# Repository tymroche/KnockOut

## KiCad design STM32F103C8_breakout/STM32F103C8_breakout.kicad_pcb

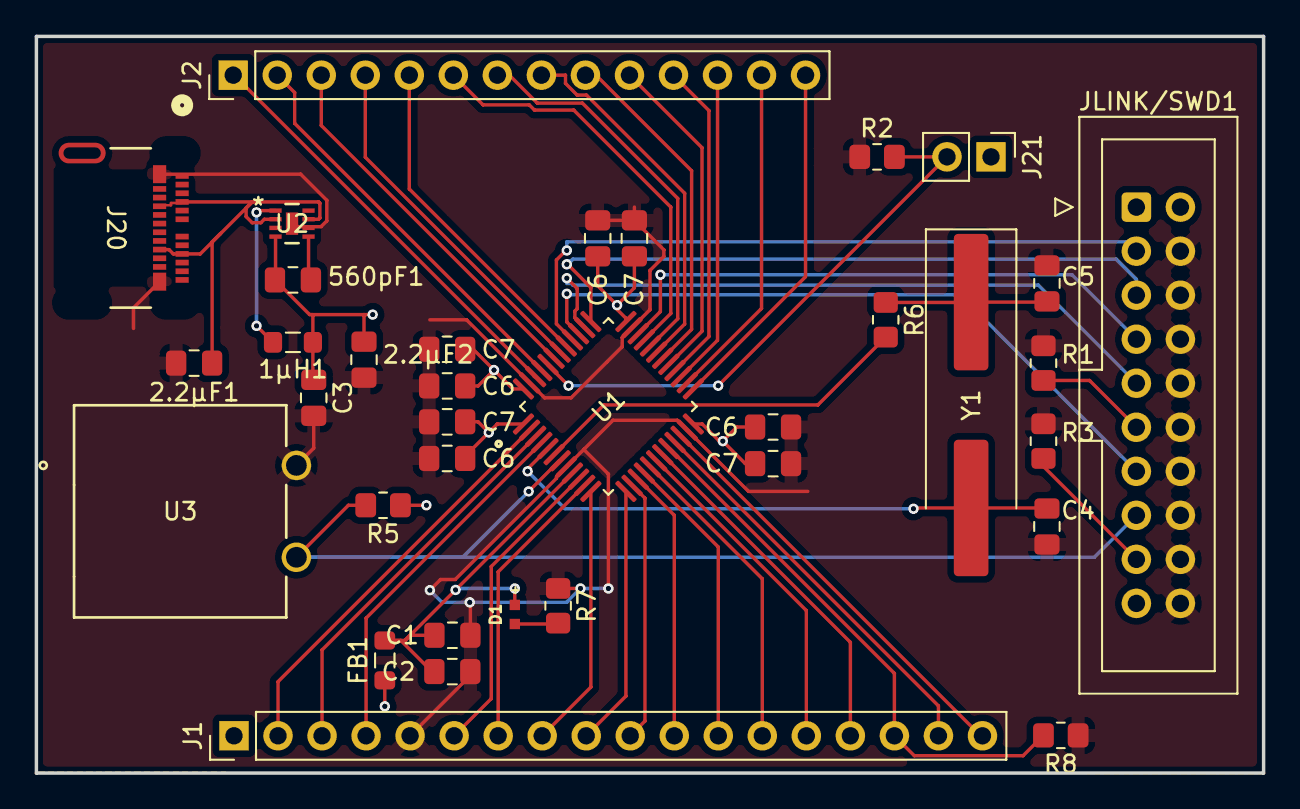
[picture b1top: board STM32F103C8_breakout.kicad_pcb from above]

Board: 2 copper layers, 70.8 x 42.5 mm, 35 parts (0 on the bottom side), 49 nets.

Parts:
1µH1: L_Small; L_0805_2012Metric_Pad1.05x1.20mm_HandSolder
2.2µF1, 2.2µF2, 560pF1: C_Small_US; C_0805_2012Metric_Pad1.18x1.45mm_HandSolder
C1: 1μF; C_0805_2012Metric_Pad1.18x1.45mm_HandSolder
C2, C3, C6, C6#2, C6#3, C6#4: 100nF; C_0805_2012Metric_Pad1.18x1.45mm_HandSolder
C4, C5: 20pF; C_0805_2012Metric_Pad1.18x1.45mm_HandSolder
C7, C7#2, C7#3, C7#4: 10μF; C_0805_2012Metric_Pad1.18x1.45mm_HandSolder
D1: WL-SMCC_0402
FB1: FerriteBead_Small; L_0805_2012Metric_Pad1.05x1.20mm_HandSolder
J1: Conn_01x18_Pin; PinHeader_1x18_P2.54mm_Vertical
J2: Conn_01x14_Pin; PinHeader_1x14_P2.54mm_Vertical
J20: USB-C; CONN_1054500101_MOL
J21: Conn_01x02_Pin; PinHeader_1x02_P2.54mm_Vertical
JLINK/SWD1: IDC-Header_2x10_P2.54mm_Vertical
R1, R2, R3, R5, R7, R8: 10kΩ; R_0805_2012Metric_Pad1.20x1.40mm_HandSolder
R6: 400Ω; R_0805_2012Metric_Pad1.20x1.40mm_HandSolder
U1: STM32F103C8T6; QFP50P900X900X160-48N
U2: BUCK_REG_3.3V; MLF-8_ML_MCH
U3: GPTS203211B; SWITCH_03211B
Y1: 16 MHz Crystal; Crystal_SMD_HC49-SD_HandSoldering

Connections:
/BOOT_IN: J21.2, R2.2, U1.44 (BOOT0)
/JNTRST: JLINK/SWD1.3 (nTRST), U1.40 (PB4)
/JTCK/SWCLK: JLINK/SWD1.9 (TCK/SWCLK), U1.38 (PA15)
/JTDI: JLINK/SWD1.5 (TDI), U1.37 (PA14)
/JTDO: JLINK/SWD1.13 (TDO/SWO), U1.39 (PB3)
/JTMS/SWDIO: JLINK/SWD1.7 (TMS/SWDIO), U1.34 (PA13)
/PA0_WKUP: J1.6, U1.10 (PA0_WKUP)
/PA1: J1.7, U1.11 (PA1)
/PA2: J1.8, U1.12 (PA2)
/PA3: J1.9, U1.13 (PA3)
/PA4: J1.10, U1.14 (PA4)
/PA5: J1.11, U1.15 (PA5)
/PA6: J1.12, U1.16 (PA6)
/PA7: J1.13, U1.17 (PA7)
/PA8: J2.10, U1.29 (PA8)
/PA9: J2.9, U1.30 (PA9)
/PA10: J2.8, U1.31 (PA10)
/PA11: J2.7, U1.32 (PA11)
/PA12: J2.6, U1.33 (PA12)
/PB0: J1.14, U1.18 (PB0)
/PB1: J1.15, U1.19 (PB1)
/PB2: J1.16, R8.2, U1.20 (PB2)
/PB5: J2.5, U1.41 (PB5)
/PB6: J2.4, U1.42 (PB6)
/PB7: J2.3, U1.43 (PB7)
/PB8: J2.2, U1.45 (PB8)
/PB9: J2.1, U1.46 (PB9)
/PB10: J1.17, U1.21 (PB10)
/PB11: J1.18, U1.22 (PB11)
/PB12: J2.14, U1.25 (PB12)
/PB13: J2.13, U1.26 (PB13)
/PB14: J2.12, U1.27 (PB14)
/PB15: J2.11, U1.28 (PB15)
/PC13: J1.2, U1.2 (PC13-TAMPER-RTC)
/PC14: J1.3, U1.3 (PC14-OSC32_IN)
/PC15: J1.4, U1.4 (PC15-OSC32_OUT)
/PowerSupply/V_IN: 2.2µF1.1, J20.A4 (VBUS), J20.A9 (VBUS), J20.B4 (VBUS), J20.B9 (VBUS), U2.2 (EN), U2.7 (VIN)
/RST_IN: JLINK/SWD1.15 (RESET), R5.2, U1.7 (NRST), U3.6
GNDREF: 2.2µF1.2, 2.2µF2.2, C1.2, C2.2, C3.2, C4.2, C5.1, C6.2, C6#2.2, C6#3.2, C6#4.2, C7.2, C7#2.2, C7#3.2, C7#4.2, J1.5, J20.A1 (GND), J20.A12 (GND), J20.B1 (GND), J20.B12 (GND), JLINK/SWD1.4 (GND), JLINK/SWD1.6 (GND), JLINK/SWD1.8 (GND), JLINK/SWD1.10 (GND), JLINK/SWD1.12 (GND), JLINK/SWD1.14 (GND*), JLINK/SWD1.16 (GND*), JLINK/SWD1.18 (GND*), JLINK/SWD1.20 (GND*), R1.2, R2.1, R3.2, R7.1, R8.1, U1.8 (VSSA), U1.23 (VSS), U1.35 (VSS), U1.47 (VSS), U2.6 (AGND), U2.8 (PGND), U2.9, U3.1
unnamed: C5.2, R6.1, Y1.1
unnamed: D1.1, R7.2
unnamed: JLINK/SWD1.17 (DBGRQ), R3.1
unnamed: JLINK/SWD1.11 (RTCK), R1.1
unnamed: C4.1, U1.5 (PD0_OSC_IN), Y1.2
unnamed: R6.2, U1.6 (PD1_OSC_OUT)
unnamed: C1.1, C2.1, D1.2, FB1.2, U1.9 (VDDA)
unnamed: 560pF1.1, U2.5 (CFF)
unnamed: 1µH1.2, U2.1 (SW)
Vdd: 1µH1.1, 2.2µF2.1, 560pF1.2, C3.1, C6.1, C6#2.1, C6#3.1, C6#4.1, C7.1, C7#2.1, C7#3.1, C7#4.1, FB1.1, J1.1, J21.1, JLINK/SWD1.1 (VTref), R5.1, U1.1 (VBAT), U1.24 (VDD), U1.36 (VDD), U1.48 (VDD), U2.4 (SNS)

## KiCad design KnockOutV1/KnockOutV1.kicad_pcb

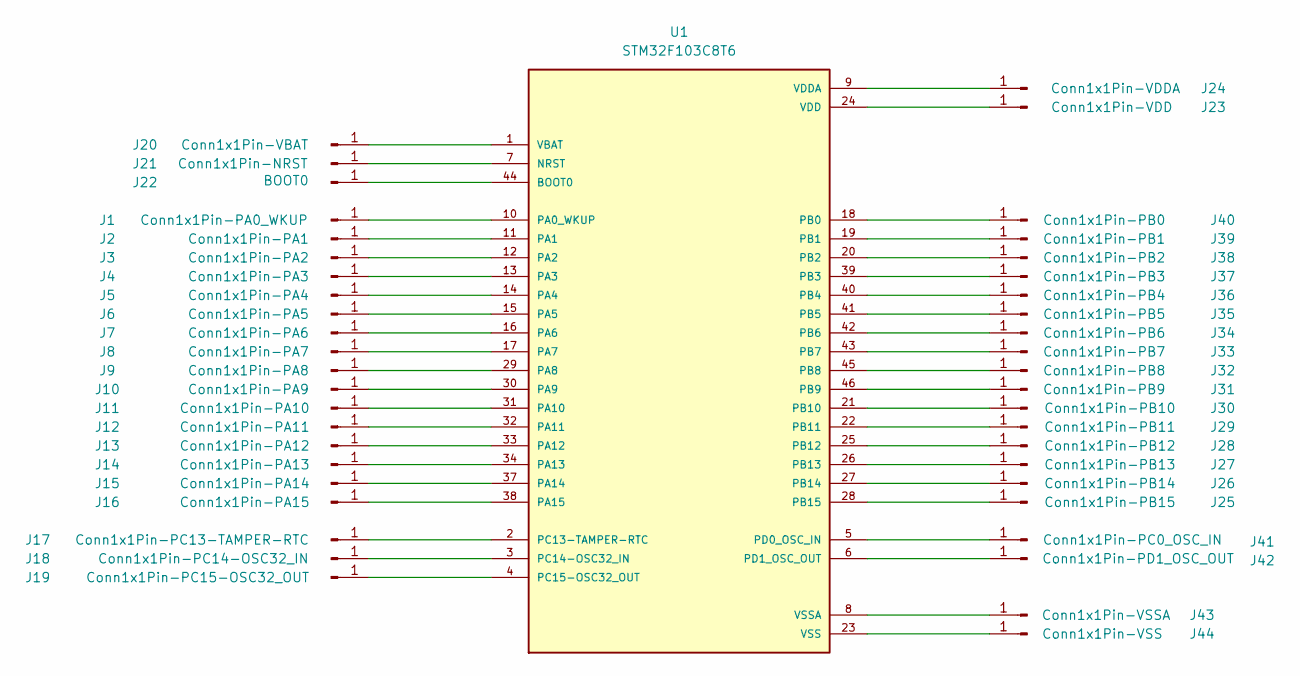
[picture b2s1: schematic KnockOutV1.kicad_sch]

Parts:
J1: Conn1x1Pin-PA0_WKUP; PinHeader_1x01_P2.54mm_Horizontal
J2: Conn1x1Pin-PA1; PinHeader_1x01_P2.54mm_Horizontal
J3: Conn1x1Pin-PA2; PinHeader_1x01_P2.54mm_Horizontal
J4: Conn1x1Pin-PA3; PinHeader_1x01_P2.54mm_Horizontal
J5: Conn1x1Pin-PA4; PinHeader_1x01_P2.54mm_Horizontal
J6: Conn1x1Pin-PA5; PinHeader_1x01_P2.54mm_Horizontal
J7: Conn1x1Pin-PA6; PinHeader_1x01_P2.54mm_Horizontal
J8: Conn1x1Pin-PA7; PinHeader_1x01_P2.54mm_Horizontal
J9: Conn1x1Pin-PA8; PinHeader_1x01_P2.54mm_Horizontal
J10: Conn1x1Pin-PA9; PinHeader_1x01_P2.54mm_Horizontal
J11: Conn1x1Pin-PA10; PinHeader_1x01_P2.54mm_Horizontal
J12: Conn1x1Pin-PA11; PinHeader_1x01_P2.54mm_Horizontal
J13: Conn1x1Pin-PA12; PinHeader_1x01_P2.54mm_Horizontal
J14: Conn1x1Pin-PA13; PinHeader_1x01_P2.54mm_Horizontal
J15: Conn1x1Pin-PA14; PinHeader_1x01_P2.54mm_Horizontal
J16: Conn1x1Pin-PA15; PinHeader_1x01_P2.54mm_Horizontal
J17: Conn1x1Pin-PC13-TAMPER-RTC; PinHeader_1x01_P2.54mm_Horizontal
J18: Conn1x1Pin-PC14-OSC32_IN; PinHeader_1x01_P2.54mm_Horizontal
J19: Conn1x1Pin-PC15-OSC32_OUT; PinHeader_1x01_P2.54mm_Horizontal
J20: Conn1x1Pin-VBAT; PinHeader_1x01_P2.54mm_Horizontal
J21: Conn1x1Pin-NRST; PinHeader_1x01_P2.54mm_Horizontal
J22: BOOT0; PinHeader_1x01_P2.54mm_Horizontal
J23: Conn1x1Pin-VDD; PinHeader_1x01_P2.54mm_Horizontal
J24: Conn1x1Pin-VDDA; PinHeader_1x01_P2.54mm_Horizontal
J25: Conn1x1Pin-PB15; PinHeader_1x01_P2.54mm_Horizontal
J26: Conn1x1Pin-PB14; PinHeader_1x01_P2.54mm_Horizontal
J27: Conn1x1Pin-PB13; PinHeader_1x01_P2.54mm_Horizontal
J28: Conn1x1Pin-PB12; PinHeader_1x01_P2.54mm_Horizontal
J29: Conn1x1Pin-PB11; PinHeader_1x01_P2.54mm_Horizontal
J30: Conn1x1Pin-PB10; PinHeader_1x01_P2.54mm_Horizontal
J31: Conn1x1Pin-PB9; PinHeader_1x01_P2.54mm_Horizontal
J32: Conn1x1Pin-PB8; PinHeader_1x01_P2.54mm_Horizontal
J33: Conn1x1Pin-PB7; PinHeader_1x01_P2.54mm_Horizontal
J34: Conn1x1Pin-PB6; PinHeader_1x01_P2.54mm_Horizontal
J35: Conn1x1Pin-PB5; PinHeader_1x01_P2.54mm_Horizontal
J36: Conn1x1Pin-PB4; PinHeader_1x01_P2.54mm_Horizontal
J37: Conn1x1Pin-PB3; PinHeader_1x01_P2.54mm_Horizontal
J38: Conn1x1Pin-PB2; PinHeader_1x01_P2.54mm_Horizontal
J39: Conn1x1Pin-PB1; PinHeader_1x01_P2.54mm_Horizontal
J40: Conn1x1Pin-PB0; PinHeader_1x01_P2.54mm_Horizontal
J41: Conn1x1Pin-PC0_OSC_IN; PinHeader_1x01_P2.54mm_Horizontal
J42: Conn1x1Pin-PD1_OSC_OUT; PinHeader_1x01_P2.54mm_Horizontal
J43: Conn1x1Pin-VSSA; PinHeader_1x01_P2.54mm_Horizontal
J44: Conn1x1Pin-VSS; PinHeader_1x01_P2.54mm_Horizontal
U1: STM32F103C8T6; QFP50P900X900X160-48N; PARTREV 10; DigiKey_Part_Number 497-6063-ND

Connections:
unnamed: J1.1, U1.10 (PA0_WKUP)
unnamed: J2.1, U1.11 (PA1)
unnamed: J3.1, U1.12 (PA2)
unnamed: J4.1, U1.13 (PA3)
unnamed: J5.1, U1.14 (PA4)
unnamed: J6.1, U1.15 (PA5)
unnamed: J7.1, U1.16 (PA6)
unnamed: J8.1, U1.17 (PA7)
unnamed: J9.1, U1.29 (PA8)
unnamed: J10.1, U1.30 (PA9)
unnamed: J11.1, U1.31 (PA10)
unnamed: J12.1, U1.32 (PA11)
unnamed: J13.1, U1.33 (PA12)
unnamed: J14.1, U1.34 (PA13)
unnamed: J15.1, U1.37 (PA14)
unnamed: J16.1, U1.38 (PA15)
unnamed: J17.1, U1.2 (PC13-TAMPER-RTC)
unnamed: J18.1, U1.3 (PC14-OSC32_IN)
unnamed: J19.1, U1.4 (PC15-OSC32_OUT)
unnamed: J20.1, U1.1 (VBAT)
unnamed: J21.1, U1.7 (NRST)
unnamed: J22.1, U1.44 (BOOT0)
unnamed: J24.1, U1.9 (VDDA)
unnamed: J25.1, U1.28 (PB15)
unnamed: J26.1, U1.27 (PB14)
unnamed: J27.1, U1.26 (PB13)
unnamed: J28.1, U1.25 (PB12)
unnamed: J29.1, U1.22 (PB11)
unnamed: J30.1, U1.21 (PB10)
unnamed: J31.1, U1.46 (PB9)
unnamed: J32.1, U1.45 (PB8)
unnamed: J33.1, U1.43 (PB7)
unnamed: J34.1, U1.42 (PB6)
unnamed: J35.1, U1.41 (PB5)
unnamed: J36.1, U1.40 (PB4)
unnamed: J37.1, U1.39 (PB3)
unnamed: J38.1, U1.20 (PB2)
unnamed: J39.1, U1.19 (PB1)
unnamed: J40.1, U1.18 (PB0)
unnamed: J41.1, U1.5 (PD0_OSC_IN)
unnamed: J42.1, U1.6 (PD1_OSC_OUT)
unnamed: J43.1, U1.8 (VSSA)
VDD: J23.1, U1.24 (VDD), U1.36 (VDD), U1.48 (VDD); also elsewhere on the board
VSS: J44.1, U1.23 (VSS), U1.35 (VSS), U1.47 (VSS); also elsewhere on the board

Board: 2 copper layers, 49 parts (0 on the bottom side), 44 nets, no tracks yet.

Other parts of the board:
J23#2, J23#3: Conn1x1Pin-VDD; PinHeader_1x01_P2.54mm_Horizontal
J44#2, J44#3: Conn1x1Pin-VSS; PinHeader_1x01_P2.54mm_Horizontal

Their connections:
VDD: J23#2.1, J23#3.1; also elsewhere on the board
VSS: J44#2.1, J44#3.1; also elsewhere on the board

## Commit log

2026-03-19 Initial Commit
    Files Created
2026-03-20 Added STM_Breakout and Documentation Files
2026-03-20 Began Schematic Pin Breakout
2026-03-20 PCB Pin Breakouts Finished
2026-03-24 Rearraged Files
2026-04-09 Refactored Dev. Board Schematic
2026-04-09 Updated schematic to (mostly) complete Dev Board.
2026-05-21 Added STM32 BluePill Test Code. Configured VSCode to program STM successfully.
2026-05-21 Added Obsidian Vault
2026-05-21 Added BluePill Documents
2026-05-28 Added to Schematics
2026-05-29 Updated Boot Switch from SPDT to Jumper Functionality
2026-06-06 Worked on PCB Layout
2026-06-06 Added any unsaved changes
2026-06-07 Completed PCB Layoutx
2026-06-08 Finalized PCB Design. Ready for Review.
2026-06-08 Added Documentation
2026-06-11 Organized Folders
2026-06-11 Moved STM Reference Doc
2026-06-11 KnockOutV1 High Level Diagram Added
2026-06-12 Added State Machine FW Document
2026-06-17 Added decoupling capacitors for every Vdd net on STM chip.
2026-06-17 Added gitignore
2026-06-19 Connected Ferrite Bead + Fixed Cap. Values for Decoupling
2026-06-23 Placed capacitor for battery input
2026-06-23 Filled Zones
2026-06-23 Added HW & State Machine Diagrams
2026-06-27 Began schematic of KnockOutV1
